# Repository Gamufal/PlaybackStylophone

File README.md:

# PlaybackStylophone
Stylofon oparty na mikrokontrolerze z możliwością odtworzenia zapisanego wcześniej utworu.

## Cel projektu
Celem jest samodzielne zaprojektowanie i wykonanie własnej wersji stylofonu opartego na mikrokontrolerze, zainspirowanej klasycznym instrumentem elektronicznym z ubiegłego wieku, a jednocześnie wzbogaconej o możliwości, jakie daje współczesna technologia cyfrowa. Realizacja urządzenia ma na celu rozwinięcie umiejętności z zakresu elektroniki, programowania oraz syntezy dźwięku.

## Funkcjonalności:
- Generowanie elektronicznego dźwięku o stałej, syntetycznej barwie
- Regulacja głośności dźwięku
- Regulacja wysokości tonu
- Nagrywanie utworu muzyczneczo
- Odtwarzanie wcześniej nagranej kompozycji
- Zapisywanie ustawień i utworu do pamięci  
- Prezentowanie informacji na wbudowanym wyświetlaczu
- Intuicyjna obsługa ekranu za pomocą przycisków 
- Przenośność dzięki wbudowanemu zasilaniu bateryjnemu
- Szybki start i gotowość do grania po uruchomieniu
- Modułowość umożliwiająca łatwą naprawę w razie uszkodzenia komponentów

## Płytka drukowana

## Mikrokontroler 
Urządzenie wykorzystuje [Raspberry Pi Pico 2](https://www.raspberrypi.com/products/raspberry-pi-pico-2). 

## Kompatybilność
Urządzenie jest kompatybilne z wszystkimi mikrokontrolerami serii Pico od Raspberry Pi. 

## Jak uruchomić urządzenie?
1.	Podłącz baterię 9V typu 6LR61 do gniazda zasilania.
2.	Włącz urządzenie za pomocą przełącznika zlokalizowanego w prawym górnym rogu obudowy.
3.	Po włączeniu:
    - Zapali się zielona dioda LED.
    - Aktywuje się ekran wyświetlacza.
4.	Urządzenie jest gotowe do pracy.
5.	Aby wygenerować dźwięk, dotknij metalowego klawisza przy pomocy stylusu, zostanie odtworzony odpowiedni ton muzyczny.

## Autor
Kamil Kotorc - *Gamufal*

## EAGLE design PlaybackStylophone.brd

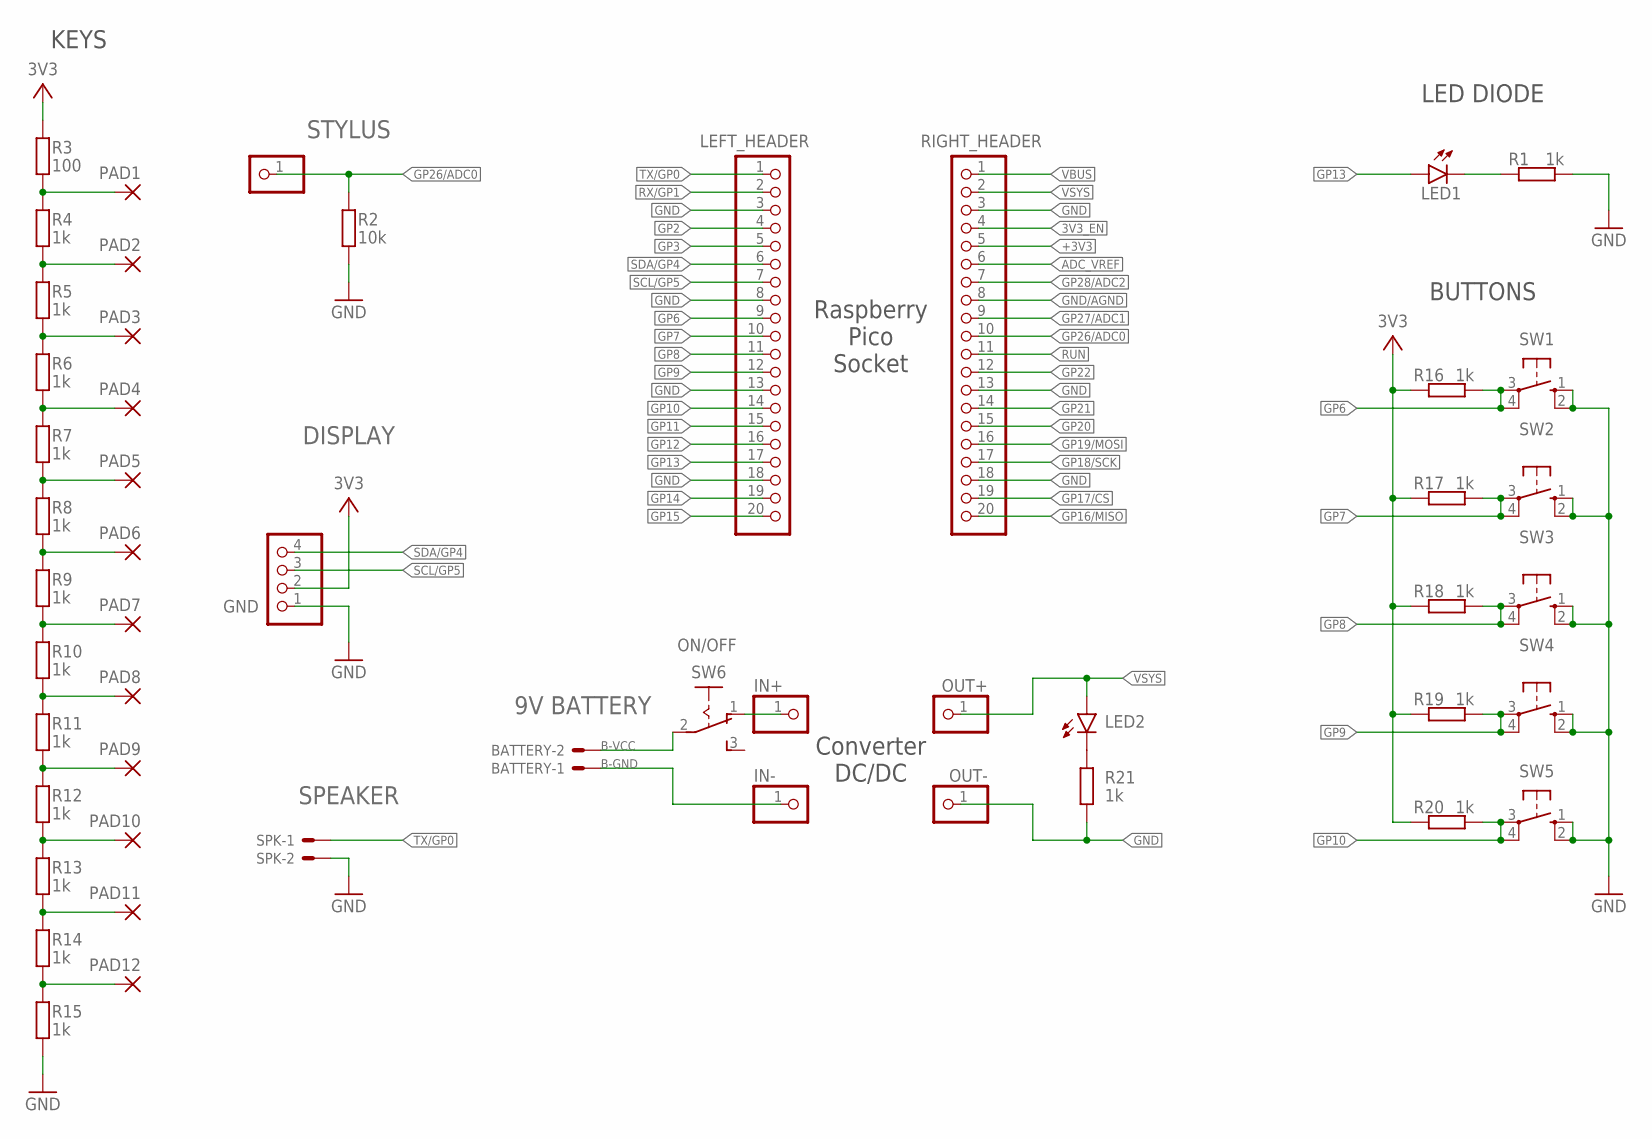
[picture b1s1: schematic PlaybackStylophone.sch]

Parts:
BATTERY: 9V BATTERY; 22-23-2021
DISPLAY: GND; 1X04
IN+: PINHD-1X1; 1X01
IN-: PINHD-1X1; 1X01
LED1: LED5MM
LED2: LED3MM
LEFT_HEADER: PINHD-1X20; 1X20
OUT+: PINHD-1X1; 1X01
OUT-: PINHD-1X1; 1X01
PAD1, PAD2, PAD3, PAD4, PAD5, PAD6, PAD7, PAD8, PAD9, PAD10, PAD11, PAD12: SMD5; SMD2,54-5,08
R1, R4, R5, R6, R7, R8, R9, R10, R11, R12, R13, R14, R15, R16, R17, R18, R19, R20, R21: 1k; 0204/7
R2: 10k; 0204/7
R3: 100; 0204/7
RIGHT_HEADER: PINHD-1X20; 1X20
SPK: SPEAKER; 22-23-2021
STYLUS: PINHD-1X1; 1X01
SW1, SW2, SW3, SW4, SW5: 10-XX; B3F-10XX
SW6: ON/OFF; 255SB

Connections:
3V3_EN: RIGHT_HEADER.4
+3V3: DISPLAY.2, R3.2, R16.2, R17.2, R18.2, R19.2, R20.2, RIGHT_HEADER.5
ADC_VREF: RIGHT_HEADER.6
B-GND: BATTERY.1, IN-.1
B-SW: IN+.1, SW6.1 (O)
B-VCC: BATTERY.2, SW6.2
GND: DISPLAY.1, LEFT_HEADER.3, LEFT_HEADER.8, LEFT_HEADER.13, LEFT_HEADER.18, OUT-.1, R1.1, R2.1, R15.1, R21.1, RIGHT_HEADER.3, RIGHT_HEADER.13, RIGHT_HEADER.18, SPK.2, SW1.1 (S), SW1.2 (S1), SW2.1 (S), SW2.2 (S1), SW3.1 (S), SW3.2 (S1), SW4.1 (S), SW4.2 (S1), SW5.1 (S), SW5.2 (S1)
GND/AGND: RIGHT_HEADER.8
GP2: LEFT_HEADER.4
GP3: LEFT_HEADER.5
GP6: LEFT_HEADER.9, R16.1, SW1.3, SW1.4 (P1)
GP7: LEFT_HEADER.10, R17.1, SW2.3, SW2.4 (P1)
GP8: LEFT_HEADER.11, R18.1, SW3.3, SW3.4 (P1)
GP9: LEFT_HEADER.12, R19.1, SW4.3, SW4.4 (P1)
GP10: LEFT_HEADER.14, R20.1, SW5.3, SW5.4 (P1)
GP11: LEFT_HEADER.15
GP12: LEFT_HEADER.16
GP13: LED1.A, LEFT_HEADER.17
GP14: LEFT_HEADER.19
GP15: LEFT_HEADER.20
GP16/MISO: RIGHT_HEADER.20
GP17/CS: RIGHT_HEADER.19
GP18/SCK: RIGHT_HEADER.17
GP19/MOSI: RIGHT_HEADER.16
GP20: RIGHT_HEADER.15
GP21: RIGHT_HEADER.14
GP22: RIGHT_HEADER.12
GP26/ADC0: R2.2, RIGHT_HEADER.10, STYLUS.1
GP27/ADC1: RIGHT_HEADER.9
GP28/ADC2: RIGHT_HEADER.7
LED: LED1.K (C), R1.2
unnamed: LED2.K (C), R21.2
P1: PAD1.1, R3.1, R4.2
P2: PAD2.1, R4.1, R5.2
P3: PAD3.1, R5.1, R6.2
P4: PAD4.1, R6.1, R7.2
P5: PAD5.1, R7.1, R8.2
P6: PAD6.1, R8.1, R9.2
P7: PAD7.1, R9.1, R10.2
P8: PAD8.1, R10.1, R11.2
P9: PAD9.1, R11.1, R12.2
P10: PAD10.1, R12.1, R13.2
P11: PAD11.1, R13.1, R14.2
P12: PAD12.1, R14.1, R15.2
RUN: RIGHT_HEADER.11
RX/GP1: LEFT_HEADER.2
SCL/GP5: DISPLAY.3, LEFT_HEADER.7
SDA/GP4: DISPLAY.4, LEFT_HEADER.6
TX/GP0: LEFT_HEADER.1, SPK.1
VBUS: RIGHT_HEADER.1
VSYS: LED2.A, OUT+.1, RIGHT_HEADER.2

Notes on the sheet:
Raspberry Pico Socket
KEYS
LED DIODE
BUTTONS
Converter DC/DC

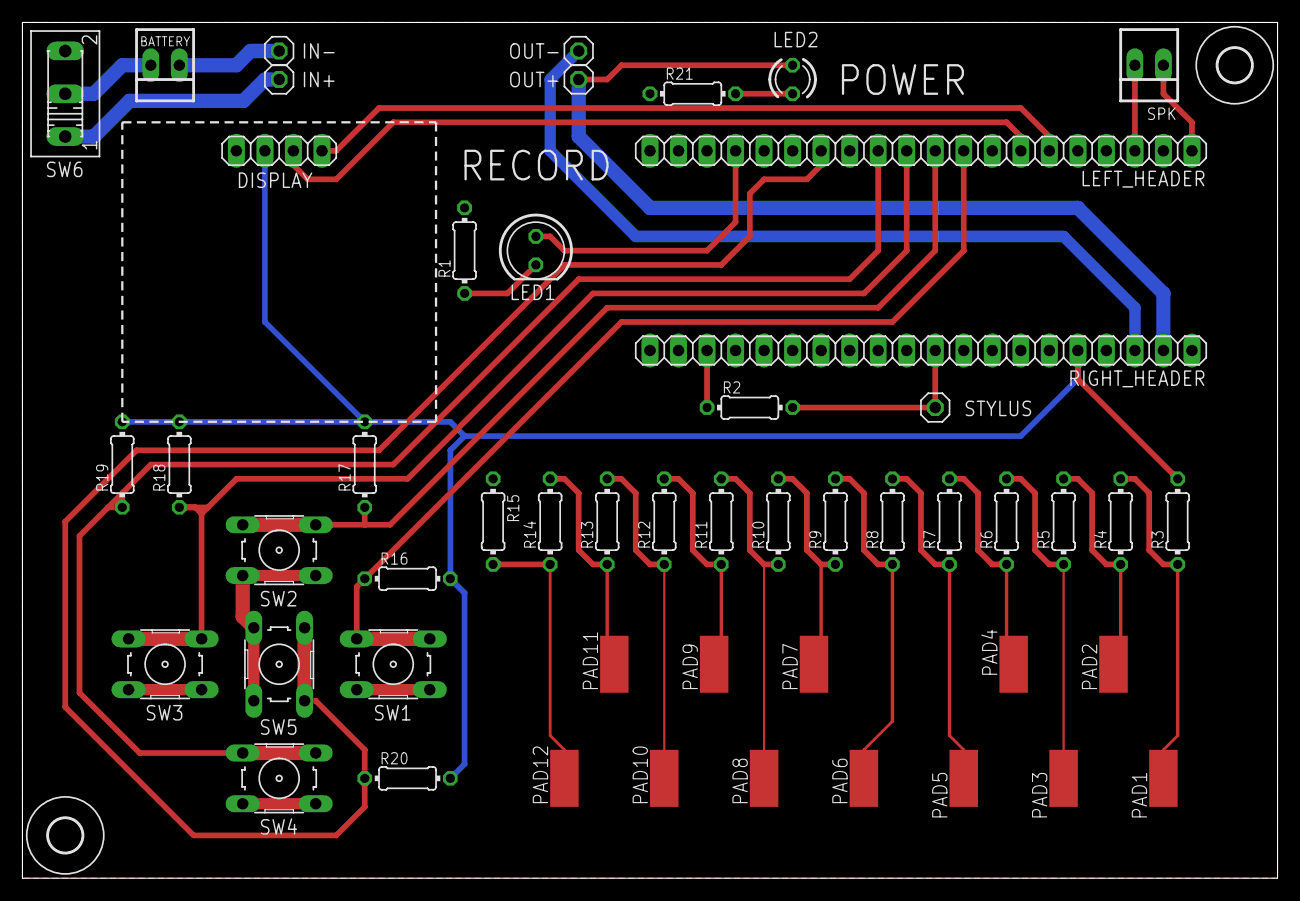
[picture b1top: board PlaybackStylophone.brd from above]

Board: 2 copper layers, 111.8 x 76.2 mm, 53 parts (0 on the bottom side), 30 nets.

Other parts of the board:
U$1, U$2: 3,0

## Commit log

2025-07-26 Added AUTODESK files
    includes schematic, pcb layout and library
2025-07-26 Added software for Pico
2025-07-26 Added circuit schematic in PDF
2025-07-30 Added Documentation in Polish
    Version 1
2025-07-31 Modified Documentation
    version 2
2025-07-31 Deleted Styphone-schematic.pdf
2025-07-31 Added updated circuit schematic
2025-07-31 Updated AUTODESK files
2025-07-31 Added image of PCB layers
2025-07-31 Added image of top layer
2025-07-31 Added image of bottom layer
2025-08-01 Updated the software
2025-08-01 Updated the documentation
2025-08-11 Added PCB layers images in PNG
2025-08-12 Optimized routes layout on pcb
2025-08-12 Updated PCB images
2025-08-12 Added PCB manufacture images
2025-08-12 Added low-pass filter
2025-08-12 Updated PCB design images
2025-08-12 Updated PCB manufacture images
2025-08-12 Updated schematic
2025-08-13 Updated schematic and pcb layout in documentation
2025-08-15 Deleted obsolete Stylophone_Schematic.pdf
    PlaybackStylophone_Schematic is the new file for schematic
2025-08-15 Deleted obsolete .bmp files
2025-08-15 Deleted obsolete pcb image files
2025-08-16 Updated functionality in README.md
2025-08-17 Added image of PCB routes layout
2025-08-17 Renamed the file to better reflect its role
2025-08-20 Added PCB tp README.md
